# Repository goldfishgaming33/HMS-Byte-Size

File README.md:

# ABOUT

- I decided to take on this project when I realised I had nothing better to do over the summer
- I wanted to make use of skills I learnt while building a different device for a school competition which was a satellite in the size of a can
- I learnt to solder better, code better on the Raspberry Pi platform and design a PCB
- RC models and boats have always interested me, so I decided to combine the two to create HMS Byte Size
- The system will operate on the Raspberry Pi Zero 2W, communicating over 2.4GHz RF with a secondary Pi which will control the boat remotely
- I wasn't too confident with SMD and lacking a hot plate or any SMD capability, I decided to go with all through hole components

_LED will power to confirm the board is running_

_Careful planning of how to power such project took place and resulted in numerous de-coupling capacitors, and others to manage current spikes and back-EMI_

_2-layer PCB composed of all through hole components, will full layer ground pours, and via stitching_

_Compact 3D printed design for easy assembly_

## Costs
It's looking rather costly

I've tried to stick to amazon and ali express for cheap components, but obviously I have doubts about reliability and whatnot.

Things like resistors and capacitors through MouserUK and RapidElectronics

## BOM

It's a bit messy, I just add as I go. All accurate though

https://1drv.ms/x/c/58d29176c16c150d/ESuSnoqv2EdMtOshy8H60zMBzeC2gvnFj-rfRvqEexovow?e=tm9gPX

Screenshot

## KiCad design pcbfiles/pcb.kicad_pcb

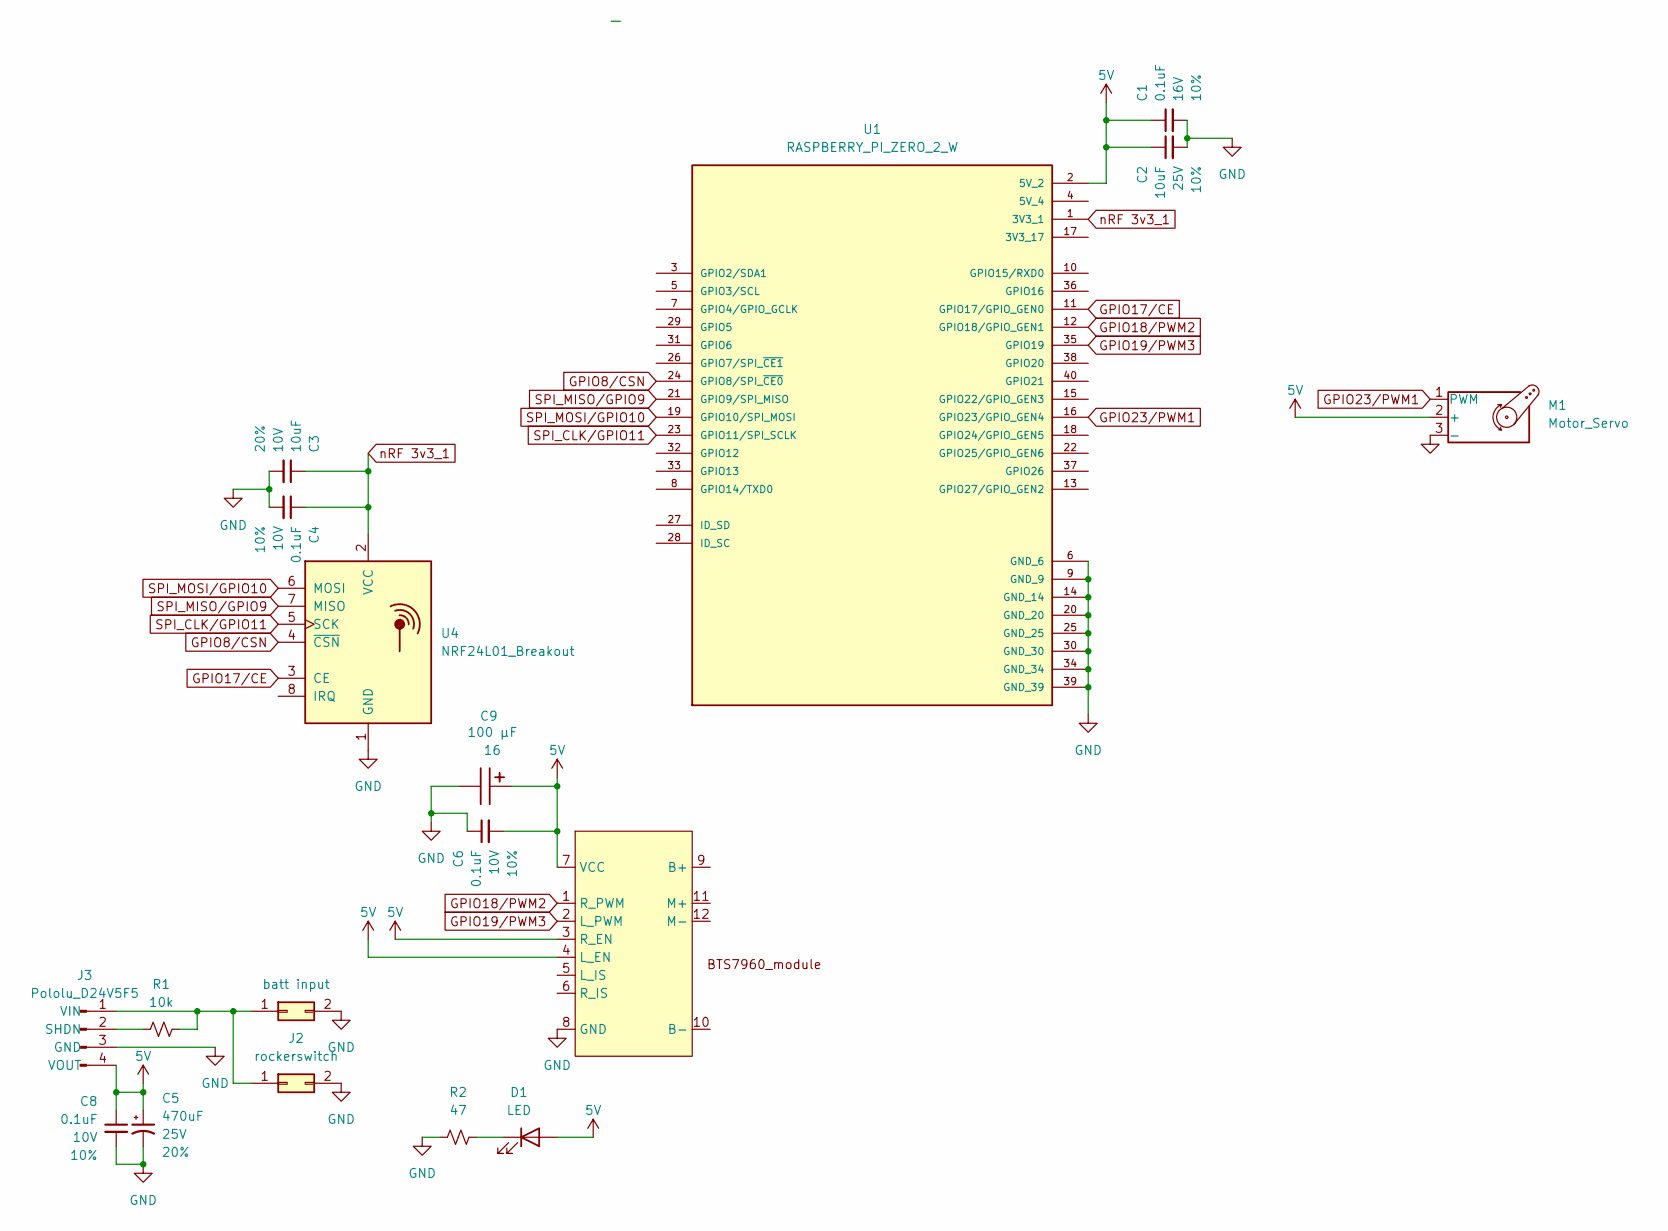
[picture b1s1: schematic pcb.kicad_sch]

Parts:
C1: 0.1uF; C_Disc_D5.1mm_W3.2mm_P5.00mm; Voltage 16V; Tolerance 10%
C2: 10uF; C_Disc_D5.1mm_W3.2mm_P5.00mm; Voltage 25V; Tolerance 10%
C3: 10uF; C_Disc_D5.1mm_W3.2mm_P5.00mm; Voltage 10V; Tolerance 20%
C4, C6, C8: 0.1uF; C_Disc_D5.1mm_W3.2mm_P5.00mm; Voltage 10V; Tolerance 10%
C5: 470uF; CP_Wurth_WCAP-ATG8-P3.5D8L11.5; Voltage 25V; Tolerance 20%
C9: P2D5L11_860010372006; CP_Wurth_WCAP-ATG8-P2D5L11; Voltage 16; Part Number 860010372006
D1: LED; LED_D5.0mm
J1: batt input; PinSocket_2x01_P2.54mm_Vertical
J2: rockerswitch; PinSocket_2x01_P2.54mm_Vertical
J3: Pololu_D24V5F5; Converter_DCDC_Pololu_D24V5Fx_Horizontal (1)
M1: Motor_Servo; PinHeader_1x03_P2.54mm_Vertical
R1: 10k; R_Axial_DIN0204_L3.6mm_D1.6mm_P2.54mm_Vertical
R2: 47; R_Axial_DIN0204_L3.6mm_D1.6mm_P2.54mm_Vertical; Tolerance 1%
U1: RASPBERRY_PI_ZERO_2_W; MODULE_RASPBERRY_PI_ZERO_2_W; PARTREV April 2024
U2: PinHeader_2x04_P2.54mm_Vertical
U4: NRF24L01_Breakout; nRF24L01_Breakout

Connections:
5V: C1.1, C2.1, C5.1, C6.2, C8.1, C9.1, D1.2 (A), J3.4 (VOUT), M1.2 (+), U1.2 (5V_2), U2.3 (R_EN), U2.4 (L_EN), U2.7 (VCC)
GND: C1.2, C2.2, C3.2, C4.2, C5.2, C6.1, C8.2, C9.2, J1.2, J2.2, J3.3 (GND), M1.3 (-), R2.1, U1.6 (GND_6), U1.9 (GND_9), U1.14 (GND_14), U1.20 (GND_20), U1.25 (GND_25), U1.30 (GND_30), U1.34 (GND_34), U1.39 (GND_39), U2.8 (GND), U4.1 (GND)
GPIO8/CSN: U1.24 (GPIO8/SPI_~CE0), U4.4 (~CSN)
GPIO17/CE: U1.11 (GPIO17/GPIO_GEN0), U4.3 (CE)
GPIO18/PWM2: U1.12 (GPIO18/GPIO_GEN1), U2.1 (R_PWM)
GPIO19/PWM3: U1.35 (GPIO19), U2.2 (L_PWM)
GPIO23/PWM1: M1.1 (PWM), U1.16 (GPIO23/GPIO_GEN4)
unnamed: D1.1 (K), R2.2
unnamed: J1.1, J2.1, J3.1 (VIN), R1.2
unnamed: J3.2 (SHDN), R1.1
SPI_CLK/GPIO11: U1.23 (GPIO11/SPI_SCLK), U4.5 (SCK)
SPI_MISO/GPIO9: U1.21 (GPIO9/SPI_MISO), U4.7 (MISO)
SPI_MOSI/GPIO10: U1.19 (GPIO10/SPI_MOSI), U4.6 (MOSI)
nRF 3v3_1: C3.1, C4.1, U1.1 (3V3_1), U4.2 (VCC)

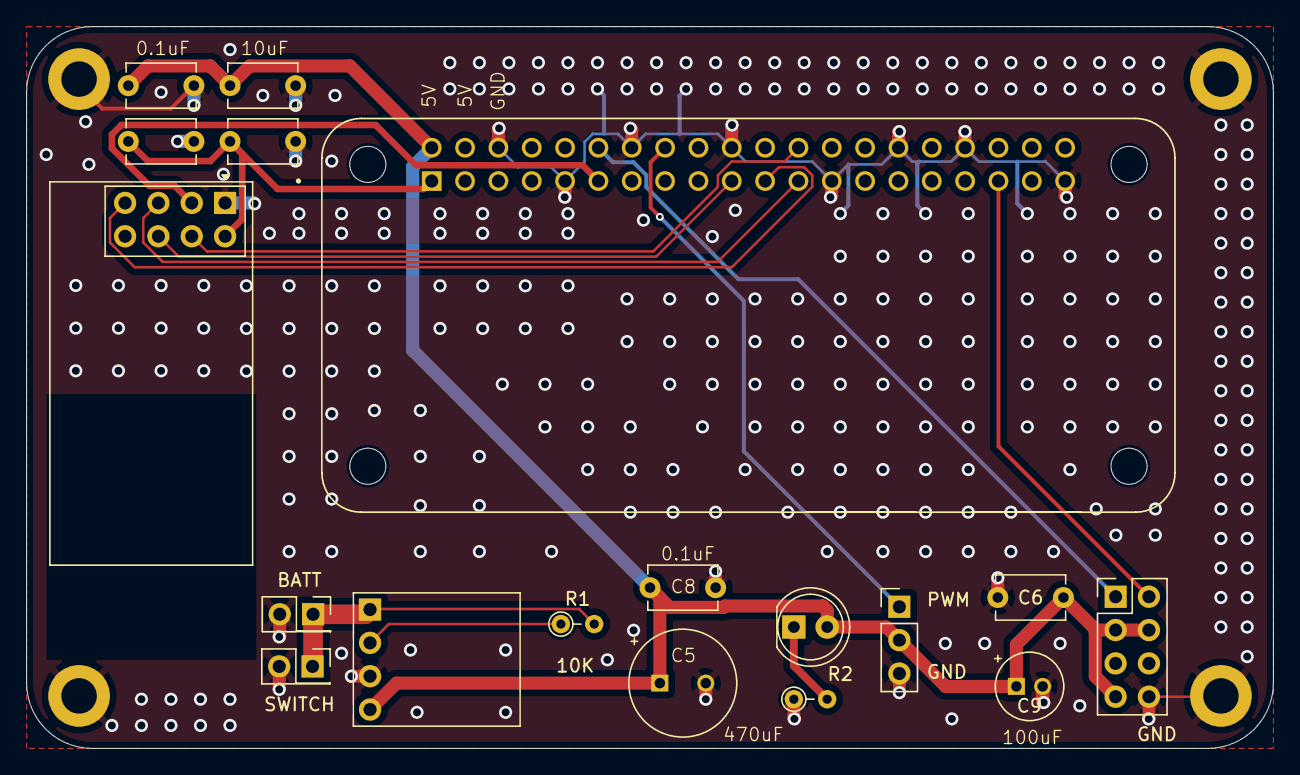
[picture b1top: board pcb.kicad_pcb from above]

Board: 2 copper layers, 95.0 x 55.0 mm, 18 parts (0 on the bottom side), 14 nets.

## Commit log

2025-06-07 Add files via upload
    BOM and PCB files added
2025-06-17 Add files via upload
    added updated pcb files
2025-06-17 Create img
2025-06-17 Update journal.md
    renamed the project
2025-06-17 updated journal and added README.md
2025-06-18 updated journal and README.md
2025-06-18 updated journal and README.md, added new images and BOM
2025-06-22 Add files via upload
    added the update pcb files in one folder
2025-06-23 updated journal, added new image
2025-06-25 updated journal and README.md, added new images
2025-06-25 updated journal and README.md, added new images and added CAD files
